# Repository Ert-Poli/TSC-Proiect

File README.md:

Prezentare Generală

OpenBook ESP32-C6 este o platformă hardware portabilă și eficientă energetic, concepută pentru aplicații embedded. Aceasta are la bază microcontrollerul ESP32-C6-WROOM-1-N8, ce oferă suport pentru Wi-Fi 6 și Bluetooth 5.0 Low Energy, precum și o varietate de interfețe pentru conectarea senzorilor și a altor module externe. Sistemul integrează un ecran e-paper, senzor de mediu BME688, ceas în timp real DS3231SN, memorie NOR Flash de 64MB, cititor pentru card microSD și un sistem de alimentare pe bază de baterie LiPo, cu încărcare integrată și monitorizare a nivelului de energie.

Bill of Materials

Componenta	Link	Datasheet
ESP32_WROVER_EAGLE-LTSPICE_RR0402	https://www.snapeda.com/parts/RC0402FR-07226RL/Yageo/view-part/	https://www.snapeda.com/parts/RC0402FR-07226RL/Yageo/datasheet/
QWIIC_CONNECTORJS-1MM	https://www.snapeda.com/parts/PRT-14417/SparkFun/view-part/	https://www.snapeda.com/parts/PRT-14417/SparkFun%20Electronics/datasheet/
BUTTON_CUSYOMV1	https://industry.panasonic.com/global/en/downloads?tab=cad&small_g_cd=203&part_no=EVQPUJ02K&q=RVZRUFVKMDJLJTdDMTMlN0MyMDMlN0MzNDU5JTdDMSU3QyU3QyU3Q2ZhbHNl	https://industry.panasonic.com/global/en/downloads?tab=catalog&small_g_cd=203&part_no=EVQPUJ02K&q=RVZRUFVKMDJLJTdDMTMlN0MyMDMlN0MzNDU5JTdDMSU3QyU3QzIlN0NmYWxzZQ%3D%3D
ESP32_WROVER_EAGLE-LTSPICE_CC0402	https://componentsearchengine.com/part-view/CC0402MRX5R5BB106/YAGEO	https://componentsearchengine.com/Datasheets/2/CC0402MRX5R5BB106.pdf
CPH3225A	https://www.snapeda.com/parts/CPH3225A/Seiko+Instruments/view-part/?ref=eda	https://www.snapeda.com/parts/CPH3225A/Seiko%20Instruments/datasheet/
ADAFRUIT_LEDCHIP-LED0603	https://www.snapeda.com/parts/KP-1608SURCK/Kingbright/view-part/?ref=search&t=LED%200603	https://www.snapeda.com/parts/KP-1608SURCK/Kingbright/datasheet/
112A-TAAR-R03_ATTEND	https://store.comet.bg/en/Catalogue/Product/43497/	https://store.comet.bg/en/Catalogue/Product/43497/
744043680IND_4828-WE-TPC_WRE	https://www.digikey.sg/en/models/1638515	https://www.we-online.com/components/products/datasheet/744043680.pdf
BD5229G-TR	https://componentsearchengine.com/part-view/BD5229G-TR/ROHM%20Semiconductor	https://datasheet.datasheetarchive.com/originals/distributors/Datasheets_SAMA/f2b9741ef86007909f138d561a359946.pdf
CPH3225A	https://www.snapeda.com/parts/CPH3225A/Seiko+Instruments/view-part/?ref=eda	https://www.snapeda.com/parts/CPH3225A/Seiko%20Instruments/datasheet/
DS3231SN	https://www.snapeda.com/parts/DS3231SN%23/Analog+Devices/view-part/?ref=eda	https://www.snapeda.com/parts/DS3231SN%23/Analog%20Devices/datasheet/
ESP32-C6-WROOM-1-N8	https://www.snapeda.com/parts/ESP32-C6-WROOM-1-N8/Espressif+Systems/view-part/?ref=eda	https://www.snapeda.com/parts/ESP32-C6-WROOM-1-N8/Espressif%20Systems/datasheet/
MCP73831	https://www.digikey.com/en/models/1874108	https://ww1.microchip.com/downloads/aemDocuments/documents/APID/ProductDocuments/DataSheets/MCP73831-Family-Data-Sheet-DS20001984H.pdf
ESP32_WROVER_BME680_BME680	https://www.snapeda.com/parts/BME680/Bosch/view-part/?welcome=home	https://www.snapeda.com/parts/BME680/Bosch%20Sensortec/datasheet/
ESP32_WROVER_EAGLE-LTSPICE_CC0402	https://componentsearchengine.com/Datasheets/2/CC0402MRX5R5BB106.pdf	https://componentsearchengine.com/part-view/CC0402MRX5R5BB106/YAGEO
ESP32_WROVER_SPARKFUN-DISCRETESEMI_MOSFET_PCH-DMG2305UX-7	https://componentsearchengine.com/part-view/DMG2305UX-7/Diodes%20Incorporated	https://www.diodes.com//assets/Datasheets/DMG2305UX.pdf
ESP32C6_VARISTORCN1812	https://www.mouser.co.uk/ProductDetail/EPCOS-TDK/B72520T0350K062?qs=dEfas%2FXlABIszF52uu7vrg%3D%3D	https://www.tdk-electronics.tdk.com/inf/75/db/CTVS_14/Surge_protection_series.pdf
FH34SRJ-24S-0.5SH_99_	https://componentsearchengine.com/part-view/XC6220A331MR-G/Torex	https://product.torexsemi.com/system/files/series/xc6220.pdf
MAX17048G+T10	https://www.snapeda.com/parts/MAX17048G+T10/Analog+Devices/view-part/?ref=eda	https://www.snapeda.com/parts/MAX17048G+T10/Analog%20Devices/datasheet/
MBR0530	https://ro.mouser.com/ProductDetail/KYOCERA-AVX/SD0805S020S1R0?qs=jCA%252BPfw4LHbpkAoSnwrdjw%3D%3D	https://ro.mouser.com/datasheet/2/40/schottky-3165252.pdf
PGB1010603MR	https://www.snapeda.com/parts/PGB1010603MR/Littelfuse/view-part/?ref=eda	https://www.snapeda.com/parts/PGB1010603MR/Littelfuse%20Inc./datasheet/
RCL_CPOL-EUCT3528	https://ro.mouser.com/ProductDetail/Vishay-Sprague/TR3B106K025C1300?qs=jCGqFXxTmLdffnuDkXzk1g%3D%3D	https://www.vishay.com/docs/40080/tr3.pdf
SAMACSYS_PARTS_USB4110-GF-A	https://componentsearchengine.com/part-view/USB4110-GF-A/GCT%20(GLOBAL%20CONNECTOR%20TECHNOLOGY)	https://gct.co/files/drawings/usb4110.pdf
SI1308EDL-T1-GE3	https://componentsearchengine.com/part-view/SI1308EDL-T1-GE3/Vishay	https://componentsearchengine.com/Datasheets/1/SI1308EDL-T1-GE3.pdf
SJ	https://grabcad.com/library/solder-jumpers-1	
USBLC6-2SC6Y	https://www.snapeda.com/parts/USBLC6-2SC6Y/STMicroelectronics/view-part/?ref=eda	https://www.snapeda.com/parts/USBLC6-2SC6Y/STMicroelectronics/datasheet/
W25Q512JVEIQ	https://www.snapeda.com/parts/W25Q512JVEIQ/Winbond+Electronics/view-part/?ref=eda	https://www.snapeda.com/parts/W25Q512JVEIQ/Winbond%20Electronics/datasheet/
XC6220A331MR-G	https://componentsearchengine.com/part-view/XC6220A331MR-G/Torex

Componente Hardware
ESP32-C6
Microcontrollerul ESP32-C6 gestionează întreaga funcționare a sistemului, inclusiv comunicarea cu perifericele, procesarea datelor și optimizarea consumului energetic.
Arhitectură RISC-V pe 32 de biți
Frecvență: până la 160 MHz
Conectivitate: Wi-Fi 6, Bluetooth 5.0
GPIO-uri versatile pentru interfețe I2C, SPI și UART

Modul RTC – DS3231SN
Ceas în timp real cu precizie ridicată și compensare termică
Funcționează independent de sistem, chiar și în mod oprit
I2C partajat cu senzorul de mediu
Senzor BME688
Măsoară temperatura, umiditatea, presiunea și compuși volatili (VOC)
Conectat pe magistrala I2C comună cu RTC
Ideal pentru analiza condițiilor ambientale și optimizarea afișajului

Ecran E-Paper
Tehnologie de afișaj pasivă, cu consum extrem de redus
Controlat prin SPI și pini RST, DC, BUSY
Dimensiune: 7.5"
Rezoluție: 800x480 px

Memorie NOR Flash – 64MB
Model W25Q512JVEIQ
Stocare SPI pentru loguri și grafice e-paper

Slot microSD
Alternativă de stocare pentru volume mari de date
Comunică prin SPI, cu chip select dedicate

Sistem de Alimentare
Intrare USB-C cu protecție ESD
Suportă baterii LiPo de 3.7V, minim 1500mAh
Încărcător: MCP73831
Monitorizare nivel baterie: MAX17048 (I2C)
Stabilizare tensiune: LDO 3.3V

Protecție și Conectivitate
USB-C cu protecție ESD și diodă Schottky pentru polaritate inversă
Asigură atât alimentare cât și transfer de date

Interfață cu Utilizatorul
Butoane tactile pentru controlul funcțiilor
Conector Qwiic pentru extinderea cu senzori I2C
GPIO-uri disponibile pentru alte extensii

Interfețe de Comunicație
SPI – utilizat pentru e-paper, card SD și memoria NOR Flash
I2C – folosit pentru BME688, DS3231SN și MAX17048
UART – debug și programare
GPIO – pentru control general și butoane
Wireless – conectivitate prin Wi-Fi 6 și BLE 5.0

Supraveghere Tensiune și Reset
Circuit de monitorizare pentru tensiunea de alimentare
Reset automat în caz de instabilitate
Afișare nivel încărcare baterie
Dimensiuni și Design Fizic
Dimensiunea plăcii PCB: aprox. 92 x 54 mm
Design compact, ideal pentru integrarea într-o carcasă personalizată

Specificații Cheie
Consum minim datorită ecranului e-paper și optimizării energetice
Suport extins pentru conectivitate wireless
Măsurători de mediu în timp real
Arhitectură modulară pentru personalizare și extindere facilă
Suport stocare externă pe card microSD

Autonomie ridicată pe baterie
Funcționalitate Software
Compatibilitate cu diverse formate de e-book-uri
Interfață intuitivă pentru citire și navigare
Sincronizare wireless cu dispozitive și servicii externe
Posibilități avansate de personalizare a experienței de utilizare
Logare și analiză a datelor de mediu

Considerații de Design
PCB optimizat pentru reducerea zgomotului electric și creșterea eficienței
Componente cu consum redus alese atent pentru fiabilitate maximă
Sisteme de protecție integrate pentru siguranță
Dimensiuni mici pentru portabilitate crescută

Conectivitate ESP32-C6

Pin ESP32-C6	Funcție	Legat la
IO0	SPI MOSI	E-paper, SD Card, Flash
IO1	SPI MISO	SD Card, Flash
IO2	SPI CLK	Toate dispozitivele SPI
IO3	SPI CS	E-paper
IO4	SPI CS	NOR Flash
IO5	SPI CS	SD Card
IO6	I2C SDA	BME688, RTC, Fuel Gauge
IO7	I2C SCL	BME688, RTC, Fuel Gauge
IO8	Buton Boot	GND prin rezistor
IO10, IO11	UART0	Programare / Debug
EN	Enable MCU	Pull-up la 3.3V

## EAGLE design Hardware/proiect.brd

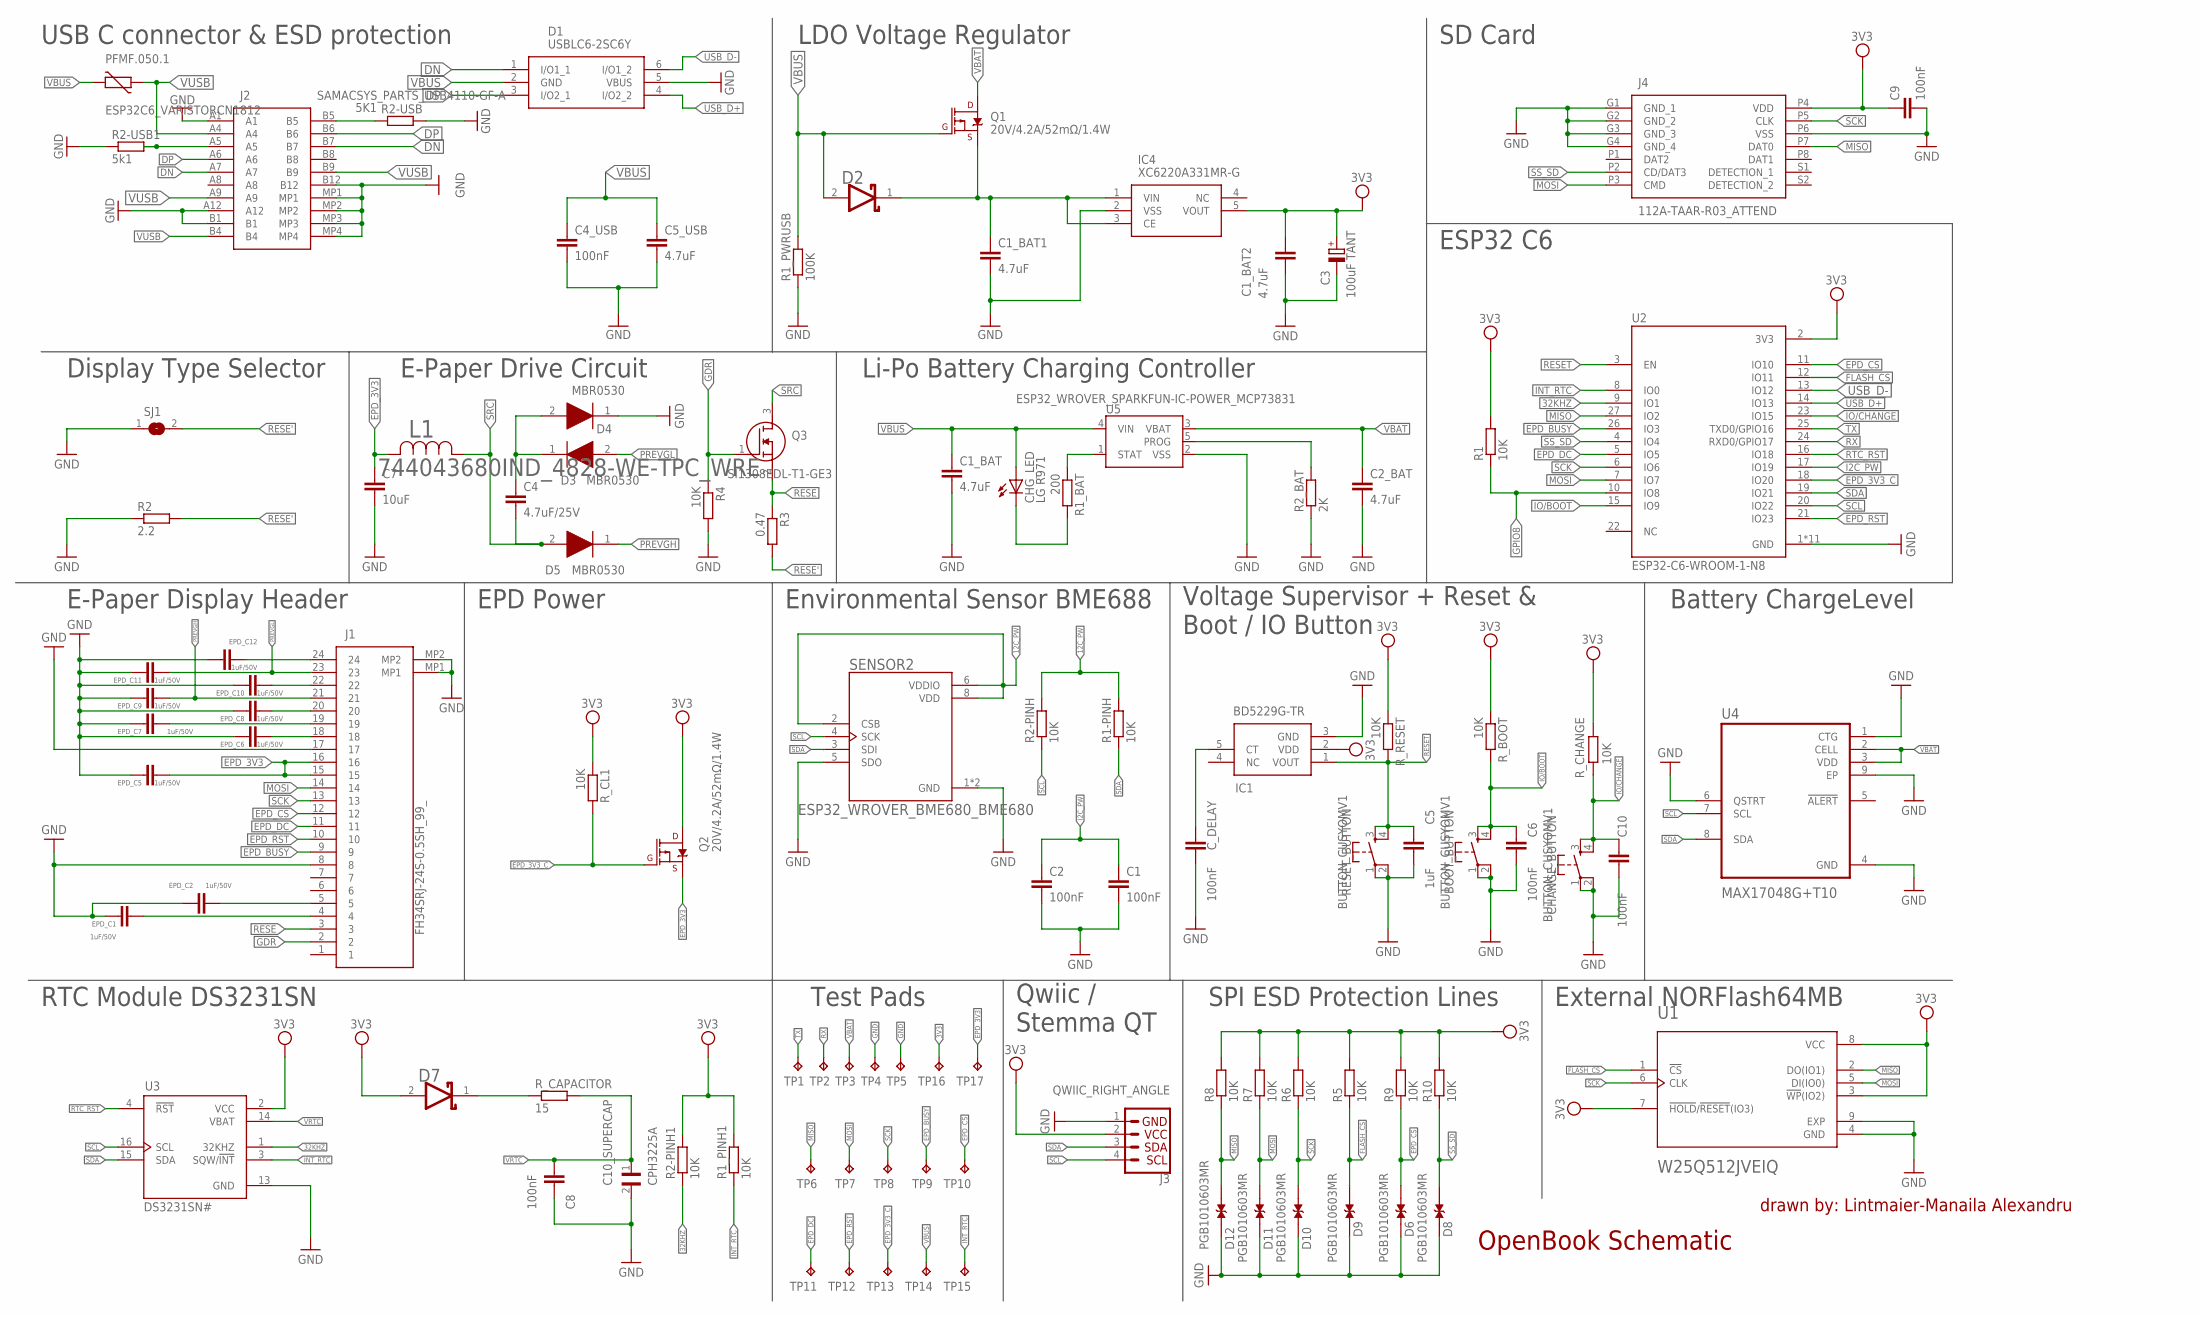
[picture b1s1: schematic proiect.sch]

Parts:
BOOT_BUTTON: BUTTON_CUSYOMV1; MYBUTTON
C1, C2, C4_USB, C6, C8, C9, C10: 100nF; EAGLE-LTSPICE_C0402
C1_BAT, C1_BAT1, C1_BAT2, C2_BAT, C5_USB: 4.7uF; EAGLE-LTSPICE_C0402
C3: 100uF TANT; RCL_CT3528
C4: 4.7uF/25V; EAGLE-LTSPICE_C0402
C5: 1uF; EAGLE-LTSPICE_C0402
C7: 10uF; EAGLE-LTSPICE_C0402
C10_SUPERCAP: CPH3225A; CAPCP3225X100N
CHANGE_BUTTON: BUTTON_CUSYOMV1; MYBUTTON
CHG_LED: LG R971; ADAFRUIT_CHIP-LED0603
C_DELAY: 100nF; EAGLE-LTSPICE_C0402
D1: USBLC6-2SC6Y; SOT95P280X145-6N
D2, D7: ESP32_WROVER_AVX---SD0805S020S1R0_AVX_SD0805S020S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; ESP32_WROVER_AVX---SD0805S020S1R0_AVX_SD0805S020S1R0_0
D3, D4, D5: MBR0530; SOD3716X135N
D6, D8, D9, D10, D11, D12: PGB1010603MR; DIOC1608X36N
EPD_C1, EPD_C2, EPD_C5, EPD_C6, EPD_C7, EPD_C8, EPD_C9, EPD_C10, EPD_C11, EPD_C12: 1uF/50V; EAGLE-LTSPICE_C0402
IC1: BD5229G-TR; SOT95P280X125-5N
IC4: XC6220A331MR-G; SOT95P280X120-5N
J1: FH34SRJ-24S-0.5SH_99_; FH34SRJ24S05SH99
J2: SAMACSYS_PARTS_USB4110-GF-A; SAMACSYS_PARTS_USB4110GFA
J3: QWIIC_RIGHT_ANGLE; JST04_1MM_RA
J4: 112A-TAAR-R03_ATTEND; 112ATAARR03ATTEND
L1: 744043680IND_4828-WE-TPC_WRE; IND_4828-WE-TPC_WRE
PFMF.050.1: ESP32C6_VARISTORCN1812; ESP32C6_VARISTOR_CT/CN1812
Q1, Q2: 20V/4.2A/52mΩ/1.4W; ESP32_WROVER_SPARKFUN-DISCRETESEMI_SOT23-3
Q3: SI1308EDL-T1-GE3; SOT65P210X110-3N
R1, R1-PINH, R1_PINH1, R2-PINH, R2-PINH1, R4, R5, R6, R7, R8, R9, R10: 10K; ESP32_WROVER_EAGLE-LTSPICE_R0402
R1_BAT: 200; ESP32_WROVER_EAGLE-LTSPICE_R0402
R1_PWRUSB: 100K; ESP32_WROVER_EAGLE-LTSPICE_R0402
R2: 2.2; ESP32_WROVER_EAGLE-LTSPICE_R0402
R2-USB: 5K1; ESP32_WROVER_EAGLE-LTSPICE_R0402
R2-USB1: 5k1; ESP32_WROVER_EAGLE-LTSPICE_R0402
R2_BAT: 2K; ESP32_WROVER_EAGLE-LTSPICE_R0402
R3: 0.47; ESP32_WROVER_EAGLE-LTSPICE_R0402
RESET_BUTTON: BUTTON_CUSYOMV1; MYBUTTON
R_BOOT: 10K; ESP32_WROVER_EAGLE-LTSPICE_R0402
R_CAPACITOR: 15; ESP32_WROVER_EAGLE-LTSPICE_R0402
R_CHANGE: 10K; ESP32_WROVER_EAGLE-LTSPICE_R0402
R_CL1: 10K; ESP32_WROVER_EAGLE-LTSPICE_R0402
R_RESET: 10K; ESP32_WROVER_EAGLE-LTSPICE_R0402
SENSOR2: ESP32_WROVER_BME680_BME680; ESP32_WROVER_BME680_PSON80P300X300X100-8N
SJ1: SJ
TP1, TP2, TP3, TP4, TP5, TP6, TP7, TP8, TP9, TP10, TP11, TP12, TP13, TP14, TP15, TP16, TP17: TPTP20R; TP20R
U1: W25Q512JVEIQ; SON127P600X800X80-9N
U2: ESP32-C6-WROOM-1-N8; XCVR_ESP32-C6-WROOM-1-N8
U3: DS3231SN#; SOIC127P1032X265-16N
U4: MAX17048G+T10; SON50P200X200X80-9N
U5: ESP32_WROVER_SPARKFUN-IC-POWER_MCP73831; ESP32_WROVER_SPARKFUN-IC-POWER_SOT23-5

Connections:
3V3: C1_BAT2.1, C3.+, C9.1, D7.2 (ANODE), IC1.2 (VDD), IC4.5 (VOUT), J3.2, J4.P4 (VDD), Q2.3 (D), R1.2, R1_PINH1.2, R2-PINH1.2, R5.2, R6.2, R7.2, R8.2, R9.2, R10.2, R_BOOT.1, R_CHANGE.1, R_CL1.1, R_RESET.1, TP16.TP, U1.3 (!WP!(IO2)), U1.7 (!HOLD!/!RESET!(IO3)), U1.8 (VCC), U2.2 (3V3), U3.2 (VCC)
12C_PW: R1-PINH.2, R2-PINH.2, SENSOR2.2 (CSB), SENSOR2.6 (VDDIO), SENSOR2.8 (VDD)
32KHZ: R2-PINH1.1, U2.9 (IO1), U3.1 (32KHZ)
DN: D1.1 (I/O1_1), J2.A7, J2.B7
DP: D1.3 (I/O2_1), J2.A6, J2.B6
EPD_3V3: C7.1, EPD_C5.2, J1.15, J1.16, L1.2, Q2.2 (S), TP17.TP
EPD_3V3_C: Q2.1 (G), R_CL1.2, TP13.TP, U2.18 (IO20)
EPD_BUSY: J1.9, TP9.TP, U2.26 (IO3)
EPD_CS: D6.2, J1.12, R9.1, TP10.TP, U2.11 (IO10)
EPD_DC: J1.11, TP11.TP, U2.5 (IO5)
EPD_RST: J1.10, TP12.TP, U2.21 (IO23)
FLASH_CS: D9.2, R5.1, U1.1 (!CS), U2.12 (IO11)
GDR: J1.2, Q3.1 (G), R4.1
GND: BOOT_BUTTON.1, BOOT_BUTTON.2, C1.2, C1_BAT.2, C1_BAT1.2, C1_BAT2.2, C2.2, C2_BAT.2, C3.-, C4_USB.2, C5.2, C5_USB.2, C6.2, C7.2, C8.2, C9.2, C10.2, C10_SUPERCAP.2, CHANGE_BUTTON.1, CHANGE_BUTTON.2, C_DELAY.2, D1.5 (VBUS), D4.1 (K), D6.1, D8.1, D9.1, D10.1, D11.1, D12.1, EPD_C1.1, EPD_C2.1, EPD_C5.1, EPD_C6.1, EPD_C7.1, EPD_C8.1, EPD_C9.1, EPD_C10.1, EPD_C11.1, EPD_C12.1, IC1.3 (GND), IC4.2 (VSS), J1.8, J1.17, J1.MP1, J1.MP2, J2.A1, J2.A12, J2.B1, J2.B12, J2.MP1, J2.MP2, J2.MP3, J2.MP4, J3.1, J4.G1 (GND_1), J4.G2 (GND_2), J4.G3 (GND_3), J4.G4 (GND_4), J4.P6 (VSS), R1_PWRUSB.1, R2.1, R2-USB.2, R2-USB1.1, R2_BAT.1, R4.2, RESET_BUTTON.1, RESET_BUTTON.2, SENSOR2.1 (GND), SENSOR2.5 (SDO), SENSOR2.7 (GND), SJ1.1, TP4.TP, TP5.TP, U1.4 (GND), U1.9 (EXP), U2.1 (GND), U2.28 (GND), U2.29_1 (GND), U2.29_2 (GND), U2.29_3 (GND), U2.29_4 (GND), U2.29_5 (GND), U2.29_6 (GND), U2.29_7 (GND), U2.29_8 (GND), U2.29_9 (GND), U3.13 (GND), U4.1 (CTG), U4.4 (GND), U4.6 (QSTRT), U4.9 (EP), U5.2 (VSS)
GPIO8: R1.1, U2.10 (IO8)
I2C_PW: C1.1, C2.1, U2.17 (IO19)
INT_RTC: R1_PINH1.1, TP15.TP, U2.8 (IO0), U3.3 (SQW/!INT)
IO/BOOT: BOOT_BUTTON.3, BOOT_BUTTON.4, C6.1, R_BOOT.2, U2.15 (IO9)
IO/CHANGE: C10.1, CHANGE_BUTTON.3, CHANGE_BUTTON.4, R_CHANGE.2, U2.23 (IO15)
MISO: D12.2, J4.P7 (DAT0), R8.1, TP6.TP, U1.2 (DO(IO1)), U2.27 (IO2)
MOSI: D11.2, J1.14, J4.P3 (CMD), R7.1, TP7.TP, U1.5 (DI(IO0)), U2.7 (IO7)
unnamed: J2.A5, R2-USB1.2
unnamed: J2.B5, R2-USB.1
unnamed: C1_BAT1.1, D2.1 (CATHODE), IC4.1 (VIN), IC4.3 (CE), Q1.2 (S)
unnamed: CHG_LED.C, R1_BAT.2
unnamed: R1_BAT.1, U5.1 (STAT)
unnamed: EPD_C1.2, J1.4
unnamed: R2_BAT.2, U5.5 (PROG)
unnamed: C4.1, D3.1 (K), D4.2 (A)
unnamed: EPD_C2.2, J1.5
unnamed: EPD_C6.2, J1.18
unnamed: EPD_C7.2, J1.19
unnamed: EPD_C8.2, J1.20
unnamed: C_DELAY.1, IC1.5 (CT)
unnamed: EPD_C10.2, J1.22
unnamed: EPD_C12.2, J1.24
unnamed: D7.1 (CATHODE), R_CAPACITOR.1
PREVGH: D5.1 (K), EPD_C9.2, J1.21
PREVGL: D3.2 (A), EPD_C11.2, J1.23
RESE: J1.3, Q3.2 (S), R3.1
RESE': R2.2, R3.2, SJ1.2
RESET: C5.1, IC1.1 (VOUT), RESET_BUTTON.3, RESET_BUTTON.4, R_RESET.2, U2.3 (EN)
RTC_RST: U2.16 (IO18), U3.4 (!RST)
RX: TP2.TP, U2.24 (RXD0/GPIO17)
SCK: D10.2, J1.13, J4.P5 (CLK), R6.1, TP8.TP, U1.6 (CLK), U2.6 (IO6)
SCL: J3.4, R2-PINH.1, SENSOR2.4 (SCK), U2.20 (IO22), U3.16 (SCL), U4.7 (SCL)
SDA: J3.3, R1-PINH.1, SENSOR2.3 (SDI), U2.19 (IO21), U3.15 (SDA), U4.8 (SDA)
SRC: C4.2, D5.2 (A), L1.1, Q3.3 (D)
SS_SD: D8.2, J4.P2 (CD/DAT3), R10.1, U2.4 (IO4)
TX: TP1.TP, U2.25 (TXD0/GPIO16)
USB_D+: D1.4 (I/O2_2), U2.14 (IO13)
USB_D-: D1.6 (I/O1_2), U2.13 (IO12)
VBAT: C2_BAT.1, Q1.3 (D), TP3.TP, U4.2 (CELL), U4.3 (VDD), U5.3 (VBAT)
VBUS: C1_BAT.1, C4_USB.1, C5_USB.1, CHG_LED.A, D1.2 (GND), D2.2 (ANODE), PFMF.050.1.2, Q1.1 (G), R1_PWRUSB.2, TP14.TP, U5.4 (VIN)
VRTC: C8.1, C10_SUPERCAP.1, R_CAPACITOR.2, U3.14 (VBAT)
VUSB: J2.A4, J2.A9, J2.B4, J2.B9, PFMF.050.1.1

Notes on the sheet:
USB C connector & ESD protection
LDO Voltage Regulator
SD Card
ESP32 C6
Li-Po Battery Charging Controller
E-Paper Drive Circuit
Display Type Selector
E-Paper Display Header
EPD Power
Environmental Sensor BME688
Voltage Supervisor + Reset & Boot / IO Button
Battery ChargeLevel
RTC Module DS3231SN
Test Pads
Qwiic / Stemma QT
SPI ESD Protection Lines
External NORFlash64MB
OpenBook Schematic
drawn by: Lintmaier-Manaila Alexandru

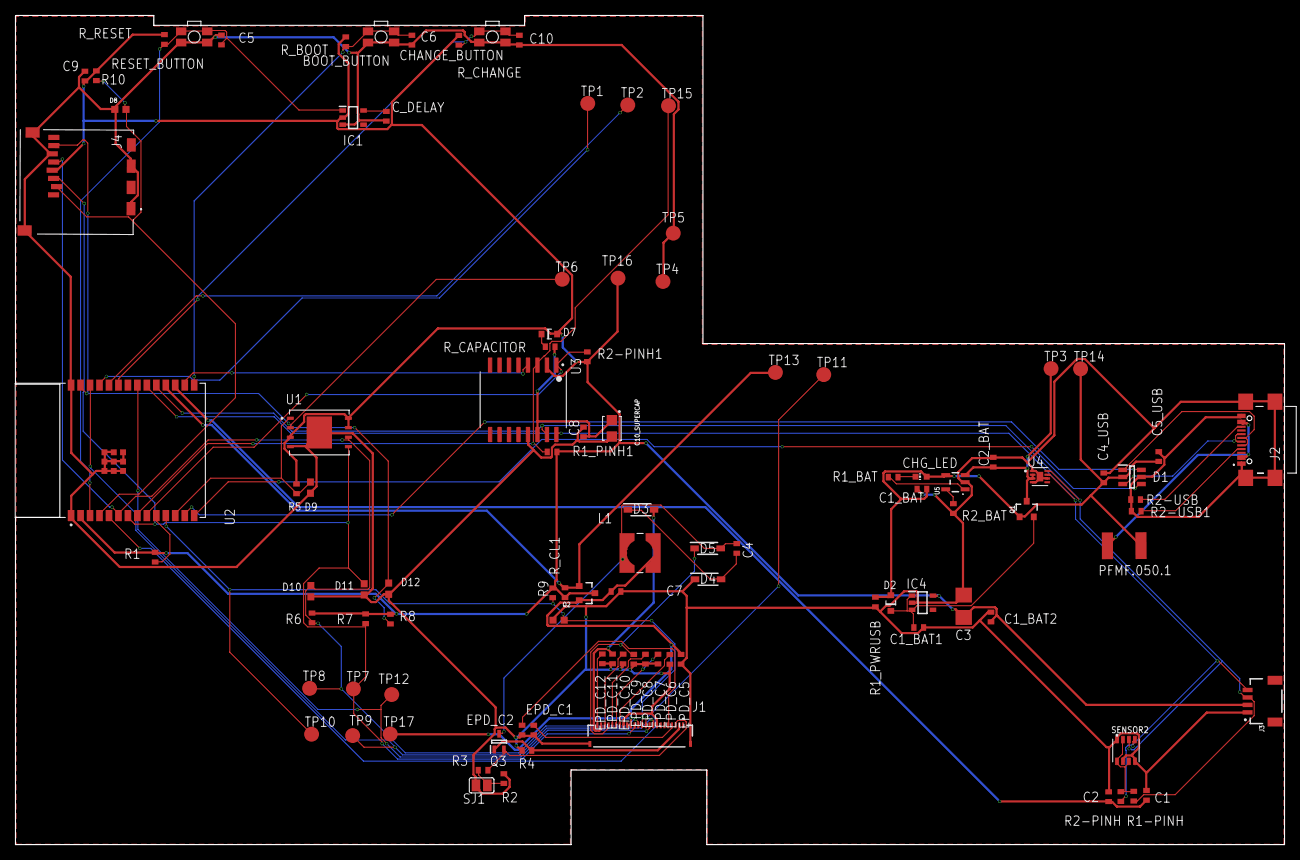
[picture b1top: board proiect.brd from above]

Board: 2 copper layers, 170.2 x 111.2 mm, 103 parts (0 on the bottom side), 56 nets.

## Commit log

2025-04-16 stergere
2025-04-16 actualizate

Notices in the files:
parts and their libraries:
COPYRIGHT: Copyright (C) 2024 Ultra Librarian. All rights reserved.
